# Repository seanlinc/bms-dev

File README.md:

## Battery Management System Dev Board for LTC68xx

This board is original develped for [Spartan Racing Electric](http://sr-e.org), any other FSAE teams and projects are welcome to use

It can directly talk to LTC68xx evaluation board via RJ-45, such as [DC2259A](https://www.analog.com/en/design-center/evaluation-hardware-and-software/evaluation-boards-kits/dc2259a.html)

MIT license, you can use or modify it as you want

### Features
* STM32F303CC6 Microcontroller
* LTC6820 Isoalted SPI interface and transformer
* TI SN65HVD232 CAN transceiver
* CP2012 USB to UART bridge
* On board DB9 connector and termination resistor
* RJ-45 connector for LTC68xx dev board
* USB-C

**About Manufacturing**

It's a 4 layers 50mm x 50mm board, which can be printed in JLC PCB cheaply in case you don't have a sponsorship

The smallest SMD size is 0603, it is designed for hand soldering and reworking

Schematic

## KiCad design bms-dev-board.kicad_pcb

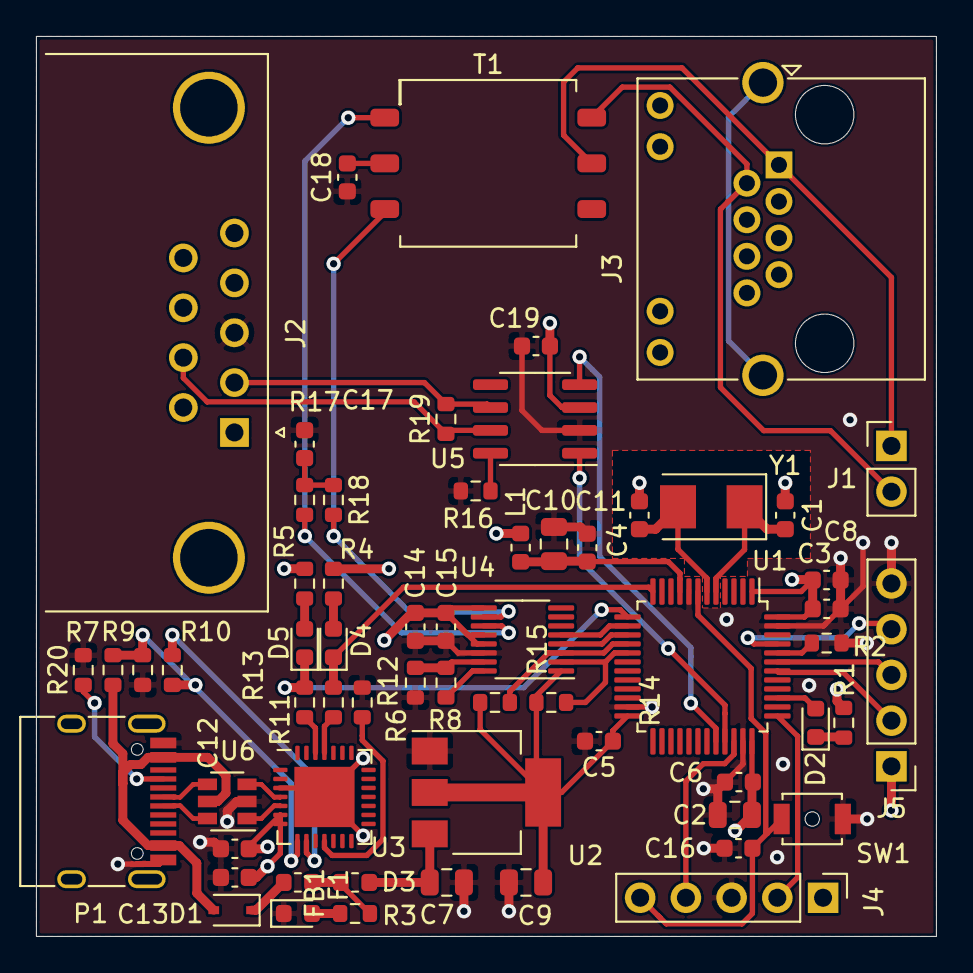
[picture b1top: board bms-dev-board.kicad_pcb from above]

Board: 4 copper layers, 50.0 x 50.0 mm, 62 parts (0 on the bottom side), 50 nets.

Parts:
C1, C4: 18p; C_0603_1608Metric
C2: 4u7; C_0805_2012Metric
C3, C5, C6, C8, C15, C19: 100n; C_0603_1608Metric
C7, C9: 10u; C_0805_2012Metric
C10: 1u; C_0805_2012Metric
C11, C17, C18: 10n; C_0603_1608Metric
C12: 4.7u; C_0603_1608Metric
C13, C16: 0.1u; C_0603_1608Metric
C14: 1u; C_0603_1608Metric
D1: BAT760-7; D_SOD-323
D2, D3, D4, D5: LED_Red; LED_0603_1608Metric
F1: 500mA; Fuse_0603_1608Metric
FB1: 100ohm @ 100MHz; L_0603_1608Metric
J1: Conn_01x02; PinHeader_1x02_P2.54mm_Vertical
J2: DB9_Female; DSUB-9_Female_Horizontal_P2.77x2.84mm_EdgePinOffset7.70mm_H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
J3: RJ45_Shielded; RJ45_Amphenol_RJHSE538X
J4: STLink; PinHeader_1x05_P2.54mm_Vertical
J5: OLED; PinHeader_1x05_P2.54mm_Vertical
L1: 39n; L_0603_1608Metric
P1: USB_C; USB_C_Receptacle_HRO_TYPE-C-31-M-12
R1, R3, R4, R5: 2.2k; R_0603_1608Metric
R2: 100k; R_0603_1608Metric
R6: 868; R_0603_1608Metric
R7: 22.1k; R_0603_1608Metric
R8: 1.2k; R_0603_1608Metric
R9: 47.5k; R_0603_1608Metric
R10: 1k; R_0603_1608Metric
R11, R13: 0; R_0603_1608Metric
R12, R16, R19: 10k; R_0603_1608Metric
R14, R15: 2k; R_0603_1608Metric
R17, R18: 51; R_0603_1608Metric
R20: 5.1k; R_0603_1608Metric
SW1: Reset; SW_SPST_B3U-1000P-B
T1: Transformer_SP_1S; Transformer_Murata_78250JC
U1: STM32F303CCTx; LQFP-48_7x7mm_P0.5mm
U2: AMS1117-3.3; SOT-223-3_TabPin2
U3: CP2102N-A02-GQFN28R; QFN-28-1EP_5x5mm_P0.5mm_EP3.35x3.35mm
U4: LTC6820; MSOP-16_3x4.039mm_P0.5mm
U5: SN65HVD230; SOIC-8_3.9x4.9mm_P1.27mm
U6: USBLC6-2SC6; SOT-23-6
Y1: 8MHz; Crystal_SMD_5032-2Pin_5.0x3.2mm

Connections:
+3.3VA: C10.1, C11.1, L1.2, U1.9
+3V3: C2.1, C3.1, C5.1, C6.1, C8.1, C9.1, C12.2, C13.2, C14.2, C15.2, C19.2, J4.1, J5.1, L1.1, R1.1, R4.1, R5.1, R10.2, R14.2, R15.2, U1.1, U1.24, U1.36, U1.48, U2.2, U3.6, U3.7, U4.1, U4.6, U4.7, U4.8, U4.9, U4.12, U4.13, U5.3
CAN_H: J2.7, R19.1, U5.7
CAN_L: J2.2, R19.2, U5.6
CAN_RX: U1.32, U5.4
CAN_TX: U1.33, U5.1
GND: C1.2, C2.2, C3.2, C4.2, C5.2, C6.2, C7.2, C8.2, C9.2, C10.2, C11.2, C12.1, C13.1, C14.1, C15.1, C16.1, C17.2, C18.1, C19.1, D3.1, J2.3, J4.3, J5.5, P1.A1, P1.A12, P1.B1, P1.B12, R2.1, R6.1, R9.2, R12.2, R16.1, R20.1, SW1.2, U1.8, U1.23, U1.35, U1.47, U2.1, U3.3, U3.29, U4.14, U5.2, U6.2
IM: R18.2, T1.3, U4.10
IP: R17.1, T1.1, U4.11
MISO: R15.1, U1.16, U4.3
MOSI: R14.1, U1.17, U4.2
NRST: C16.2, J4.5, SW1.1, U1.7
unnamed: C1.1, U1.5, Y1.1
unnamed: C4.1, U1.6, Y1.2
unnamed: C7.1, FB1.1, U2.3
unnamed: C17.1, R17.2, R18.1
unnamed: C18.2, T1.2
unnamed: D1.1, F1.1
unnamed: D2.1, R1.2
unnamed: D2.2, U1.39
unnamed: D3.2, R3.2
unnamed: D4.2, R4.2
unnamed: D5.2, R5.2
unnamed: F1.2, FB1.2, R3.1
unnamed: P1.A5, R20.2
unnamed: R2.2, U1.44
unnamed: R6.2, R8.1, U4.15
unnamed: R7.2, R9.1, U3.8
unnamed: R8.2, U4.16
unnamed: R10.1, U3.9
unnamed: R11.1, U3.26
unnamed: R12.1, U3.11
unnamed: R13.1, U3.25
unnamed: R16.2, U5.8
OLED_RST: J5.4, U1.45
OLED_SCL: J5.2, U1.42
OLED_SDA: J5.3, U1.43
SCK: U1.15, U4.4
SS: U1.14, U4.5
SWCLK: J4.2, U1.37
SWDIO: J4.4, U1.34
USB_CONN_DN: P1.A7, U6.6
USB_CONN_DP: P1.A6, U6.4
USB_DN: U3.5, U6.1
USB_DP: U3.4, U6.3
USB_RX: D5.1, R11.2, U1.13
USB_TX: D4.1, R13.2, U1.12
VBUS: D1.2, P1.A4, P1.A9, P1.B4, P1.B9, R7.1, U6.5
isoIM: J1.2, J3.2, T1.4
isoIP: J1.1, J3.1, T1.5

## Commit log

2021-03-04 Upload design files
2021-03-08 Add picture for schematic
